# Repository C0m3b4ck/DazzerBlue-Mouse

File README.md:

# DazzerBlue TRAMYS44940 Mouse in KiCAD 
[@PrinterFixer](https://www.youtube.com/@PrinterFixer)
[Video title here](VIDEO HERE - IF THERE IS NONE THEN IT IS NOT DONE)

KiCAD project with GERBER and DRILL files of the DazzerBlue TRAMYS44940 mouse PCB from 2018/09/25, remade manually by me, C0m3b4ck. All models of all components are in place, the PCB is of accurate size. The only inacurracies are the connections, which aren't 1:1 to the actual PCB. The microswitch and the rotary encoder are the exact same but from different companies (couldn't find original companies).

**The mouse is end-of-life.**

## Purpose

This repository preserves the complete investigation of the DazzerBlue TRAMYS44940 mouse hardware: project files, documentation and images.
It is intended as a technical reference for anyone analyzing, repairing, or getting inspired by the DazzerBlue TRAMYS44940 design and the V101S-based optical mouse architecture.

## GERBER, DRILL and BOM (click to download)
* [Full labelling and components](https://github.com/C0m3b4ck/DazzerBlue-Mouse/blob/main/DazzerBlue-GERBER-DRILL.7z)
* [Bill of Materials in .CSV](https://github.com/C0m3b4ck/DazzerBlue-Mouse/blob/main/DazzerBlue-BOM.csv)
## Components:
* V101S IC - [unofficial documentation made](https://github.com/C0m3b4ck/DazzerBlue-Mouse/blob/main/DOCS/V101S-unofficial.pdf),
* 2x Illinois KXM Capacitor 100uf - [documentation included](https://github.com/C0m3b4ck/DazzerBlue-Mouse/blob/main/DOCS/Omron-D2F-01-A-datasheet.pdf),
* 68ohm resistor,
* 3x Omron D2F-01 microswitch - [documentation included](https://github.com/C0m3b4ck/DazzerBlue-Mouse/blob/main/DOCS/Omron-D2F-01-A-datasheet.pdf) (same as on PCB but from a different company),
* 2-pin LED,
* 3-pin AlpsAlpine Rotary Encoder,

## Repository layout

- `DOCS/` — component datasheets and board photos.
- 'DazzerBlue-proj/DazzerBlue-proj.kicad_pro' - project file.
- 'DazzerBlue-proj' - project directory.
- `DazzerBlue-GERBER-DRILL.7z` — archived Gerber/drill package.

## Images
| | | | |
|---|---|---|---|
| <div align="center"><br><sub>PCB 3D view in KiCAD - underside.</sub></div> | <div align="center"><br><sub>PCB 3D view in KiCAD - top view.</sub></div> | <div align="center"><br><sub>PCB 3D view in KiCAD - left.</sub></div> | <div align="center"><br><sub>PCB 3D view in KiCAD - right.</sub></div> |
| <div align="center"><br><sub>The underside of the PCB.</sub></div> | <div align="center"><br><sub>View of the PCB from top.</sub></div> | <div align="center"><br><sub>View of the PCB from the left.</sub></div> | <div align="center"><br><sub>View of the PCB from the right.</sub></div> |
| <div align="center"><br><sub>The mouse case, stock photo.</sub></div> | <div align="center"><br><sub>Full mouse case and cable view from top.</sub></div> |  |  |
| <div align="center"><div align="center"><br><sub>Schematic of full circuit.</sub></div> |  |  |

## Credits

**Project made manually by C0m3b4ck from 08/07/2026 to 10/07/2026.**
* Unofficial V101S documentation written by C0m3b4ck,
* V101S and 4pin_male_5mm_10mm made by C0m3b4ck,
* Alpine Rotary Encoder from [AlpsAlpine](https://www.alpsalpine.com/j/)
* D2F-01 microswitch from [Omron](https://www.omron.com/global/en/),
* KXM Capacitor from Illinois capacitor (website shut down),

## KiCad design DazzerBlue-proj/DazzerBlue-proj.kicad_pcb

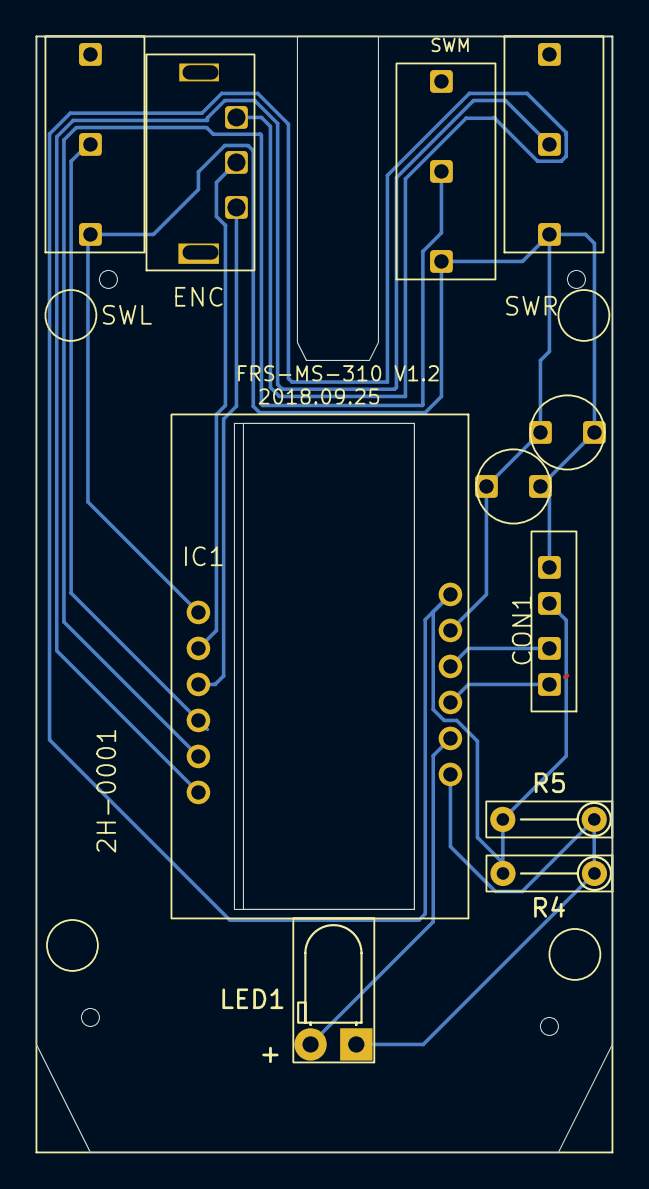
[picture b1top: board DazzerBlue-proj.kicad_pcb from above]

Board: 2 copper layers, 32.0 x 62.0 mm, 11 parts (0 on the bottom side), 12 nets.

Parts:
+: LED1; NoCourtyard_LED_D3.0mm_Horizontal_O1.27mm_Z2.0mm_Clear
C1, C2: C_Small; SmallCapacitor2
CON1: 4pin_USB_male_pins
ENC: AlpineRotaryEncoder
R4, R5: 68 ohm; NoCourtyard_R_Axial_DIN0204_L3.6mm_D1.6mm_P5.08mm_Vertical
SWL: D2FT_SW
SWM: D2FT_SW
SWR: D2FT_SW
U1: V101S

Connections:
unnamed: C2.2, U1.2 (GND)
unnamed: CON1.1 (D1), U1.4 (D1)
unnamed: CON1.2 (D2), U1.3 (D2)
unnamed: C1.1, C1.2, C2.1, CON1.4 (GND), SWL.1 (C), SWM.1 (C), SWR.1 (C), U1.7 (GND)
unnamed: CON1.3 (VCC), ENC.3 (C), R4.2, R5.2, U1.1 (VCC)
unnamed: +.2 (A), U1.5 (LED_GND)
unnamed: +.1 (K), R4.1, R5.1, U1.6 (LED_VCC)
unnamed: ENC.1 (A), U1.9 (ENC2)
unnamed: ENC.2 (B), U1.8 (ENC1)
unnamed: SWL.2 (NO), U1.10 (LBTN)
unnamed: SWM.2 (NO), U1.11 (MBTN)
unnamed: SWR.2 (NO), U1.12 (RBTN)
